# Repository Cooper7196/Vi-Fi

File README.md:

View this project on [CADLAB.io](https://cadlab.io/project/27603). 

# Vi-Fi

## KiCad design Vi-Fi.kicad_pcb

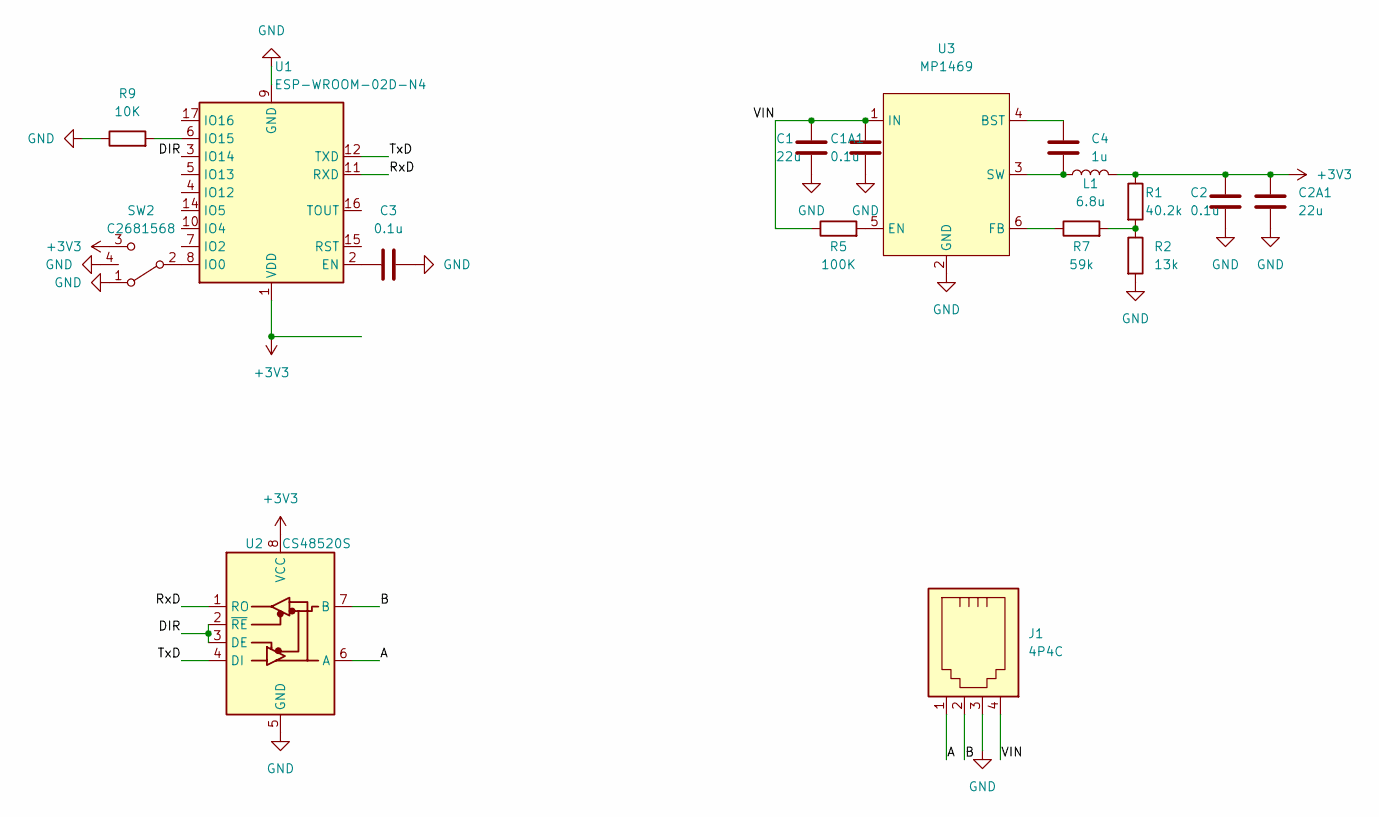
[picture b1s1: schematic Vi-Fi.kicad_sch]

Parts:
C1, C2A1: 22u; C_0805_2012Metric
C1A1, C2, C3: 0.1u; C_0603_1608Metric
C4: 1u; C_0603_1608Metric
J1: 4P4C; RJ9_Evercom_5301-440xxx_Horizontal
L1: 6.8u; L_CD73
R1: 40.2k; R_0603_1608Metric
R2: 13k; R_0603_1608Metric
R5: 100K; R_0603_1608Metric
R7: 59k; R_0603_1608Metric
R9: 10K; R_0603_1608Metric
SW2: C2681568
U1: ESP-WROOM-02D-N4; ESP-WROOM-02
U2: CS48520S; SOIC-8_3.9x4.9mm_P1.27mm
U3: MP1469; TSOT-23-6

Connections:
+3V3: C2.1, C2A1.2, L1.2, R1.1, SW2.3 (C), U1.1 (VDD), U2.8 (VCC)
/A: J1.1, U2.6 (A)
/B: J1.2, U2.7 (B)
/DIR: U1.3 (IO14), U2.2 (~RE), U2.3 (DE)
/RxD: U1.11 (RXD), U2.1 (RO)
/TxD: U1.12 (TXD), U2.4 (DI)
/VIN: C1.1, C1A1.1, J1.4, R5.1, U3.1 (IN)
GND: C1.2, C1A1.2, C2.2, C2A1.1, C3.2, J1.3, R2.2, R9.1, SW2.1 (A), SW2.4 (GND), U1.9 (GND), U1.13 (GND), U1.18 (GND), U1.19 (GND), U2.5 (GND), U3.2 (GND)
unnamed: R1.2, R2.1, R7.2
unnamed: SW2.2 (B), U1.8 (IO0)
unnamed: C3.1, U1.2 (EN)
unnamed: R9.2, U1.6 (IO15)
unnamed: C4.2, U3.4 (BST)
unnamed: R5.2, U3.5 (EN)
unnamed: R7.1, U3.6 (FB)
unnamed: C4.1, L1.1, U3.3 (SW)

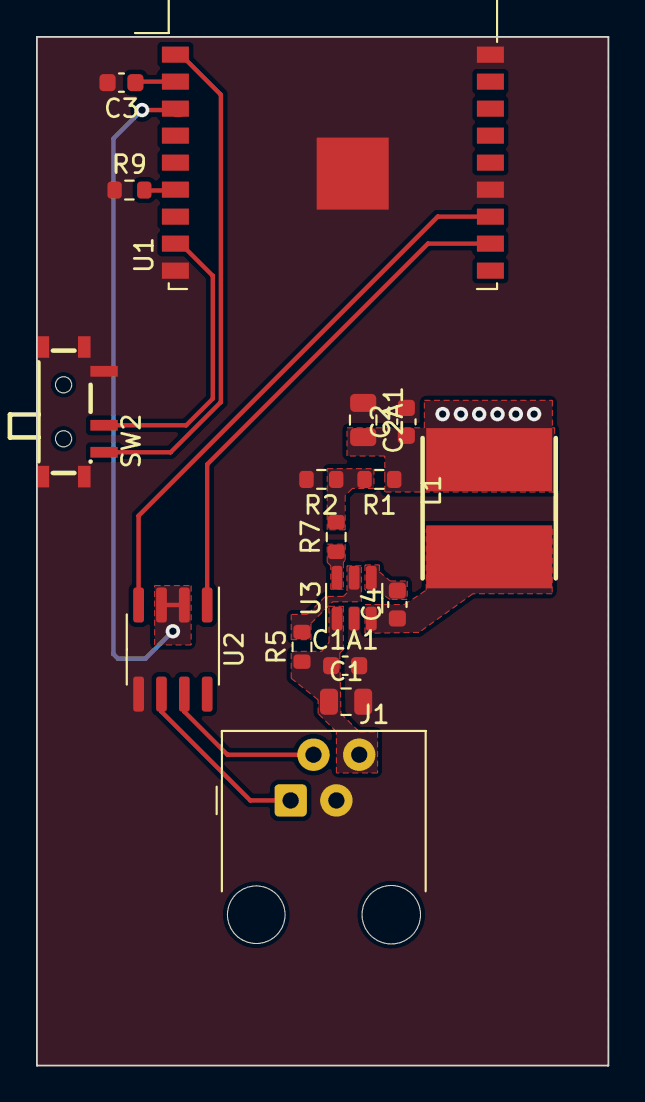
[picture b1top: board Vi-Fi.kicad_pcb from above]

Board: 2 copper layers, 31.8 x 57.1 mm, 17 parts (0 on the bottom side), 16 nets.

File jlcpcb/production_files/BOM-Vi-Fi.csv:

Comment,Designator,Footprint,LCSC
MP1469,U3,TSOT-23-6,C128217
0.1u,"C1A1,C2,C3",C_0603_1608Metric,C14663
1u,C4,C_0603_1608Metric,C15849
13k,R2,R_0603_1608Metric,C22797
59k,R7,R_0603_1608Metric,C23085
100K,R5,R_0603_1608Metric,C25803
10K,R9,R_0603_1608Metric,C25804
C2681568,SW2,C2681568,C2681568
6.8u,L1,L_CD73,C2826679
4P4C,J1,RJ9_Evercom_5301-440xxx_Horizontal,C3097715
40.2k,R1,R_0603_1608Metric,C423037
22u,"C1,C2A1",C_0805_2012Metric,C45783
CS48520S,U2,SOIC-8_3.9x4.9mm_P1.27mm,C5184817
ESP-WROOM-02D-N4,U1,ESP-WROOM-02,C529584

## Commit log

2023-12-13 Backlink to CADLAB.io has been added.
2023-12-14 Board Layout Started
